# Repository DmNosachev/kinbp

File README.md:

# KinBP
KinBP is a drop-in replacement controller for [Kinesis Contoured keyboards](https://deskthority.net/wiki/Kinesis_Contoured).

It serves the same purpose as [KinT controller](https://github.com/kinx-project/kint) created by Michael Stapelberg.

## Features and advantages
- Controller with [QMK firmware](https://qmk.fm/) support.
- Uses inexpensive [WeAct Studio STM32F401/STM32F411](https://github.com/WeActTC/MiniSTM32F4x1) MCU board. The cost of manufacturing 5 sets is about 12 USD per controller. The PCB has dimensions less than 100×100 mm. Many manufacturers provide additional discounts for smaller boards.
- Compatible with all Kinesis Contoured keyboards but the earliest models (100/110/120).
- Additional pads for connecting up to 8 swithes (i.e. additional switches on the keyboard or foot pedals).
- Replacement thumb cluster PCBs with reversible design. They may be needed for some of 13x models (see below). 
- Thumb cluster switch mounting plates.

## Changelog
1.21
- added 7-pin 1.25mm connector footprints (micro JST) for custom thumb cluster PCBs
- added spare footprints upside down for connectors with pins on the other sideю

## BOM
###  Connectors
The choice of connectors depends on the keyboard model:
 - KB600 (Advantage2).
 1. 6x 13-pin FPC connectors. [Molex 39-53-2135](https://octopart.com/39-53-2135-molex-7670149?r=sp).  Please note that the cheap (5 USD for 20 pcs) [connectors from Aliexpress](https://aliexpress.com/item/1005001616368875.html?item_id=1005001616368875&sku_id=12000016826250362&spm=a2g2w.productlist.0.0.388b79adVkSP7k) are polarised and can only be used for the top row connectors on the KB600; using them in the other positions will not work because the pads on the FPC cable are on the wrong side and the cables are too short to be twisted.

 - KB500 (Advantage).
 1. Connecting keywells and top rows: 4x 13-pin FPC connectors, same as mentioned above.
 2. Connecting thumb cluster PCBs: 2x 10-pin angled 2.54mm headers.

 - KB13x (Essential, Classic, Professional).
 1. Connecting keywell PCBs: 2x [angled 13-pin FPC connectors](https://aliexpress.com/item/32896882494.html?gatewayAdapt=glo2rus&item_id=32896882494&sku_id=65719775344&spm=a2g0s.12269583.0.0.716190456RjJJP).
 2. Connecting top rows: same angled connectors or straight (same as for KB500/KB600).
 3. Some models had LEDs on the thumb cluster PCBs instead of the controller PCB. In this case you will need a pair of new thum cluster PCBs, optional switch mounting plates (see below) and set of cables/connectors with 1.25mm pitch: 2x [7 pin micro JST 10cm cables](https://aliexpress.com/item/4000588750065.html?sku_id=10000003451067244&spm=a2g0o.store_pc_allProduct.8148356.2.6c274451oTiXZp&gatewayAdapt=glo2rus) + 4x [7 pin micro JST angled connector](https://aliexpress.com/item/4000587245338.html?spm=a2g0o.store_pc_allProduct.8148356.8.3bf42024ng7J27&pdp_npi=2%40dis%21RUB%2184%2C24%20%D1%80%D1%83%D0%B1.%2184%2C24%20%D1%80%D1%83%D0%B1.%21%21%21%21%21%40211675ce16784397398875718e4cd2%2110000003439523920%21sh&sku_id=10000003439523925).
 
 Example of incompatible stock thumb cluster PCBc (Kinesis Professional KB134PC): 
 
 You can also reuse connectors from an stock controller, but desoldering them can be tricky. Please note that the Chinese aliexpress connectors and some of the older connectors only had contacts on one side. For the top rows, you need to position the connector so that the contacts are on the outside (there are two footprints for this): 
 
### Controller PCB (/controller-pcb).
  - [WeAct Studio STM32F401 or STM32F411](https://github.com/WeActTC/MiniSTM32F4x1) board. You can buy them for about 6 USD at the [official Aliexpress store](https://weactstudio.aliexpress.com/). Beware of pirated copies!
  
  - 4 pcs 3-mm LEDs
  - 4 pcs 0805 or through-hole resistors. Their value depends on the type of LEDs (I use 1.5k Ohm for orange LEDs).
  - Pair of USB Type C male and female connectors.
###  Thumb cluster (/thumb-pcb)
  - The design is reversible. So, a minimal batch of 5 PCBs will give you 2 pairs + 1 spare.

  - 12x SOD-123 1N4148 diodes.
  - Optional [switch mounting plates](https://github.com/DmNosachev/kin80/tree/main/plates/thumb)
  - set of connectors and cables (see above)
### Switches
  - Optional: 68 pcs Cherry MX compatible switches.
  
## Buid guide
1. Test your keyboard. Identify faulty switches. Decide if you like the switches (most of the time there will Cherry Browns) and the top row rubber buttons. If rubber buttons are unacceptable to you and you do not mind spending a lot of time on hand-wiring, then it is worth considering an alternative project — (Kin80)[https://github.com/DmNosachev/kin80].
2. Disassemble the keyboard. Remove all screws and remove all PCBs. If some of the rubber buttons don't work well, the top row assembly can be taken apart and repaired by sticking pieces of copper tape on the button bottoms. Use hot-melt adhesive to asseble it back.
3. Assemble the controller PCB.
4. Optional: assemble thumb cluster PCBs.
5. Case. Seal the holes on the back of the case with pieces of plastic. Glue the USB connector to the back of the case. Optional: use bitumen sound deadening pads to improve acoustics.
6. [Setup the QMK](https://docs.qmk.fm/).
7. Flash the firmware: `qmk flash -kb kinbp -km default`. Hold 'boot0' button on MCU board, press 'reset', then release 'boot0' to enter bootloader.

## TODO
- FR4 mounting plate for the thumb cluster.
- Create universal or separate PCB with RP2040 support.

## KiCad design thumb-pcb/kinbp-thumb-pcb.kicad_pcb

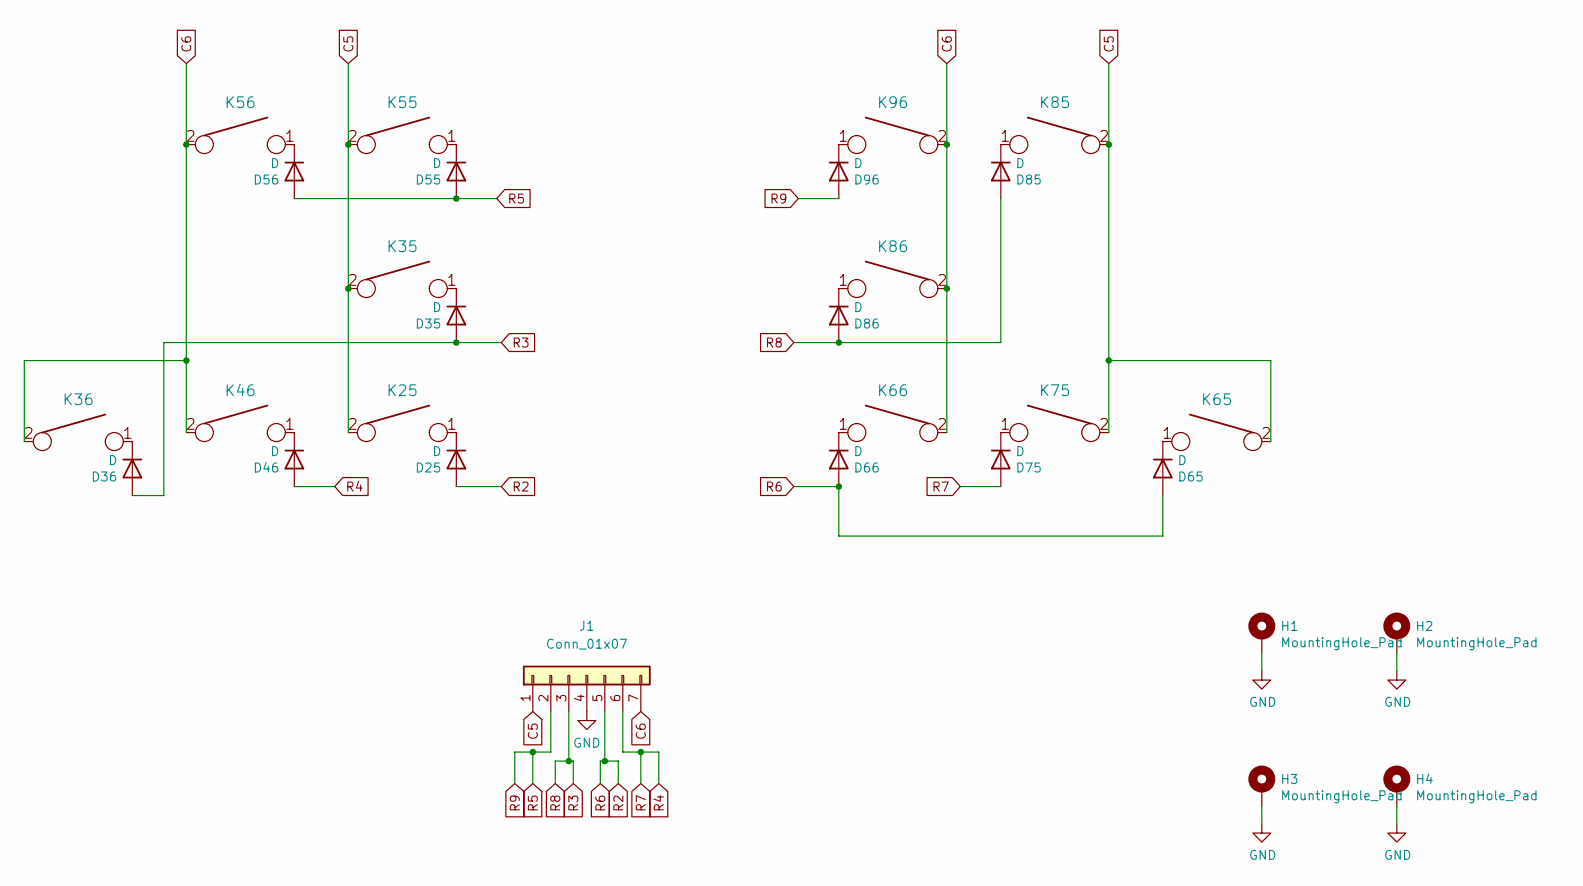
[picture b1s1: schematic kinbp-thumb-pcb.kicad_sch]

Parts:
D25, D35, D36, D46, D55, D56, D65, D66, D75, D85, D86, D96: D; D_SOD-123
H1, H2, H3, H4: MountingHole_Pad; MountingHole_3.7mm_Pad
J1: Conn_01x07; Molex_PicoBlade_53048-0710_1x07_P1.25mm_Horizontal
K25, K35, K36, K46, K55, K56: KEYSW; MXOnly-1U-NoLED-twin
K65, K66, K75, K85, K86, K96: KEYSW; MXOnly-1U-NoLED

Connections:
C5: J1.1, K25.2, K35.2, K55.2, K65.2, K75.2, K85.2
C6: J1.7, K36.2, K46.2, K56.2, K66.2, K86.2, K96.2
GND: H1.1, H2.1, H3.1, H4.1, J1.4
unnamed: D25.1 (K), K25.1
unnamed: D35.1 (K), K35.1
unnamed: D36.1 (K), K36.1
unnamed: D46.1 (K), K46.1
unnamed: D55.1 (K), K55.1
unnamed: D56.1 (K), K56.1
unnamed: D65.1 (K), K65.1
unnamed: D66.1 (K), K66.1
unnamed: D75.1 (K), K75.1
unnamed: D85.1 (K), K85.1
unnamed: D86.1 (K), K86.1
unnamed: D96.1 (K), K96.1
R2: D25.2 (A), D65.2 (A), D66.2 (A), J1.5
R3: D35.2 (A), D36.2 (A), D85.2 (A), D86.2 (A), J1.3
R4: D46.2 (A), D75.2 (A), J1.6
R5: D55.2 (A), D56.2 (A), D96.2 (A), J1.2

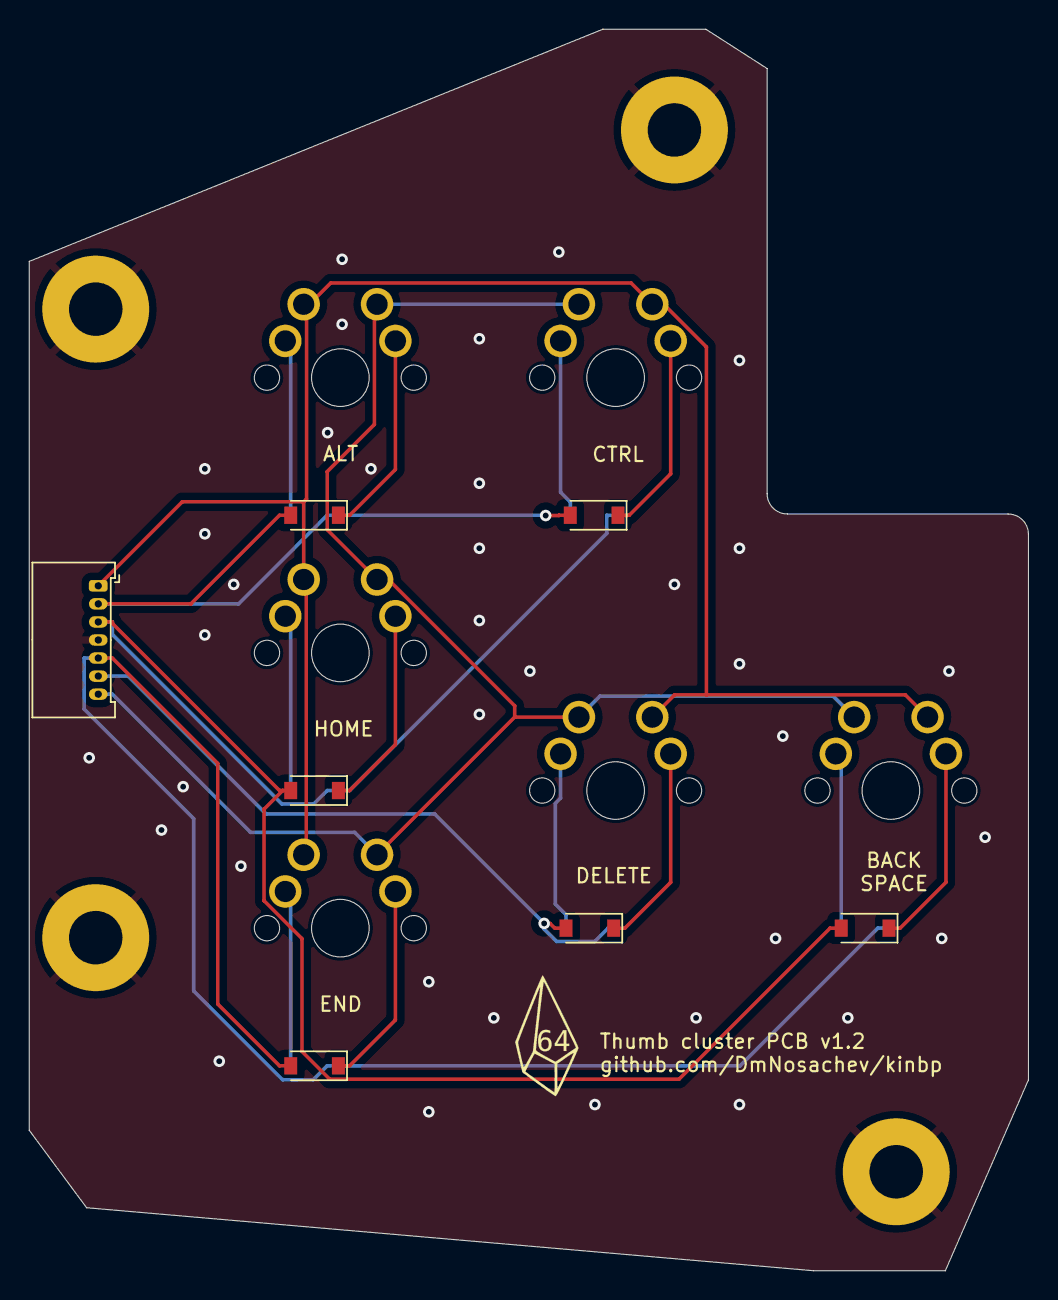
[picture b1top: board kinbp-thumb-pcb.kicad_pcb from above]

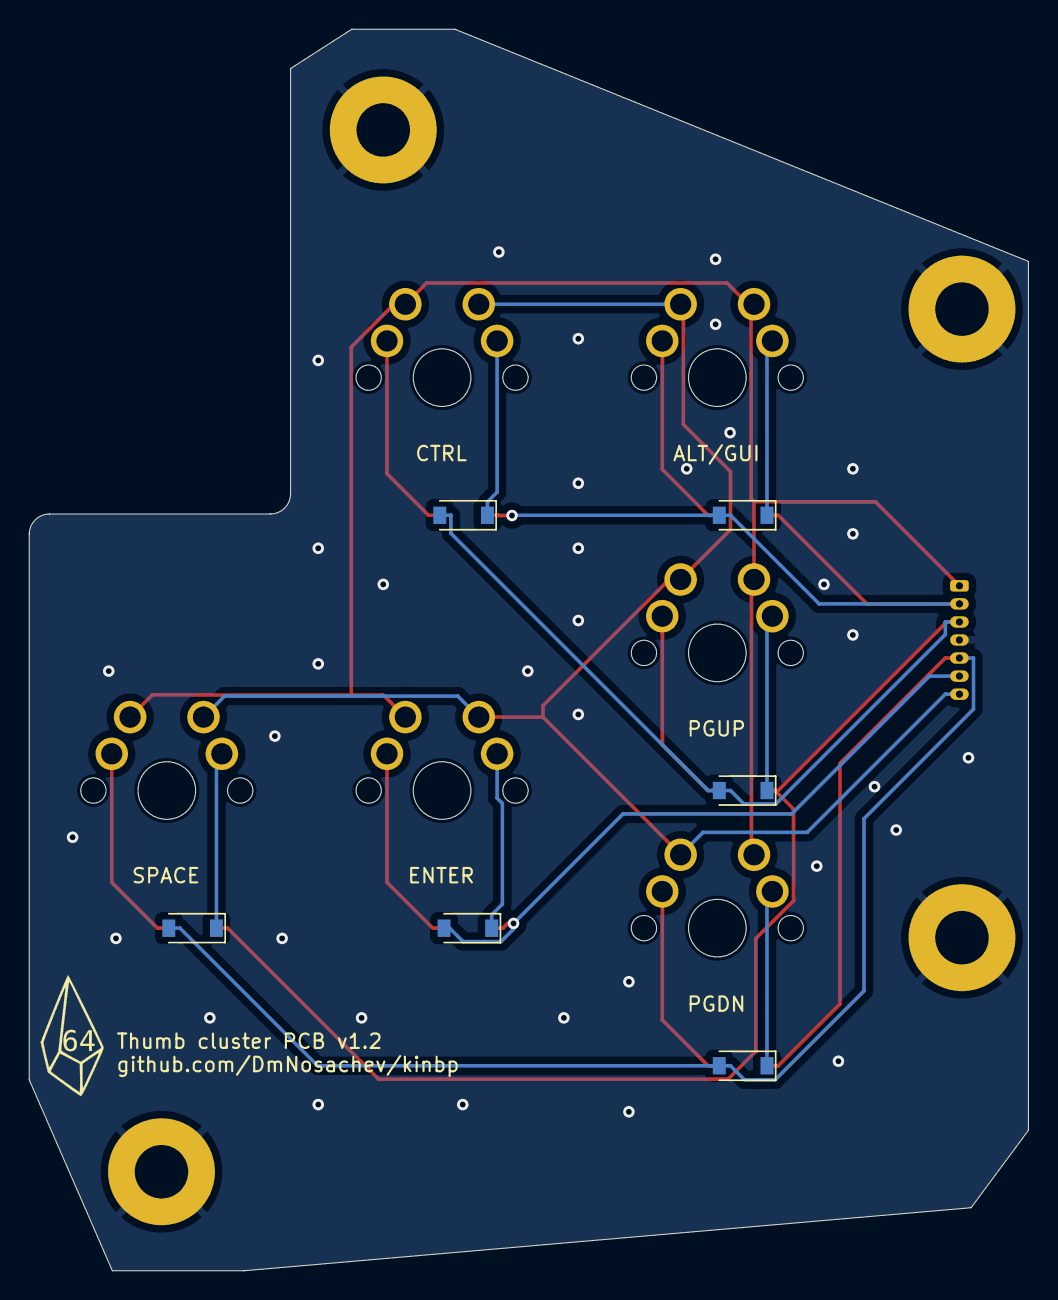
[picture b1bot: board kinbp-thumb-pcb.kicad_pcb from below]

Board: 2 copper layers, 69.2 x 85.9 mm, 31 parts (13 on the bottom side), 19 nets.

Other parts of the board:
G1, G2: LOGO; q64logo

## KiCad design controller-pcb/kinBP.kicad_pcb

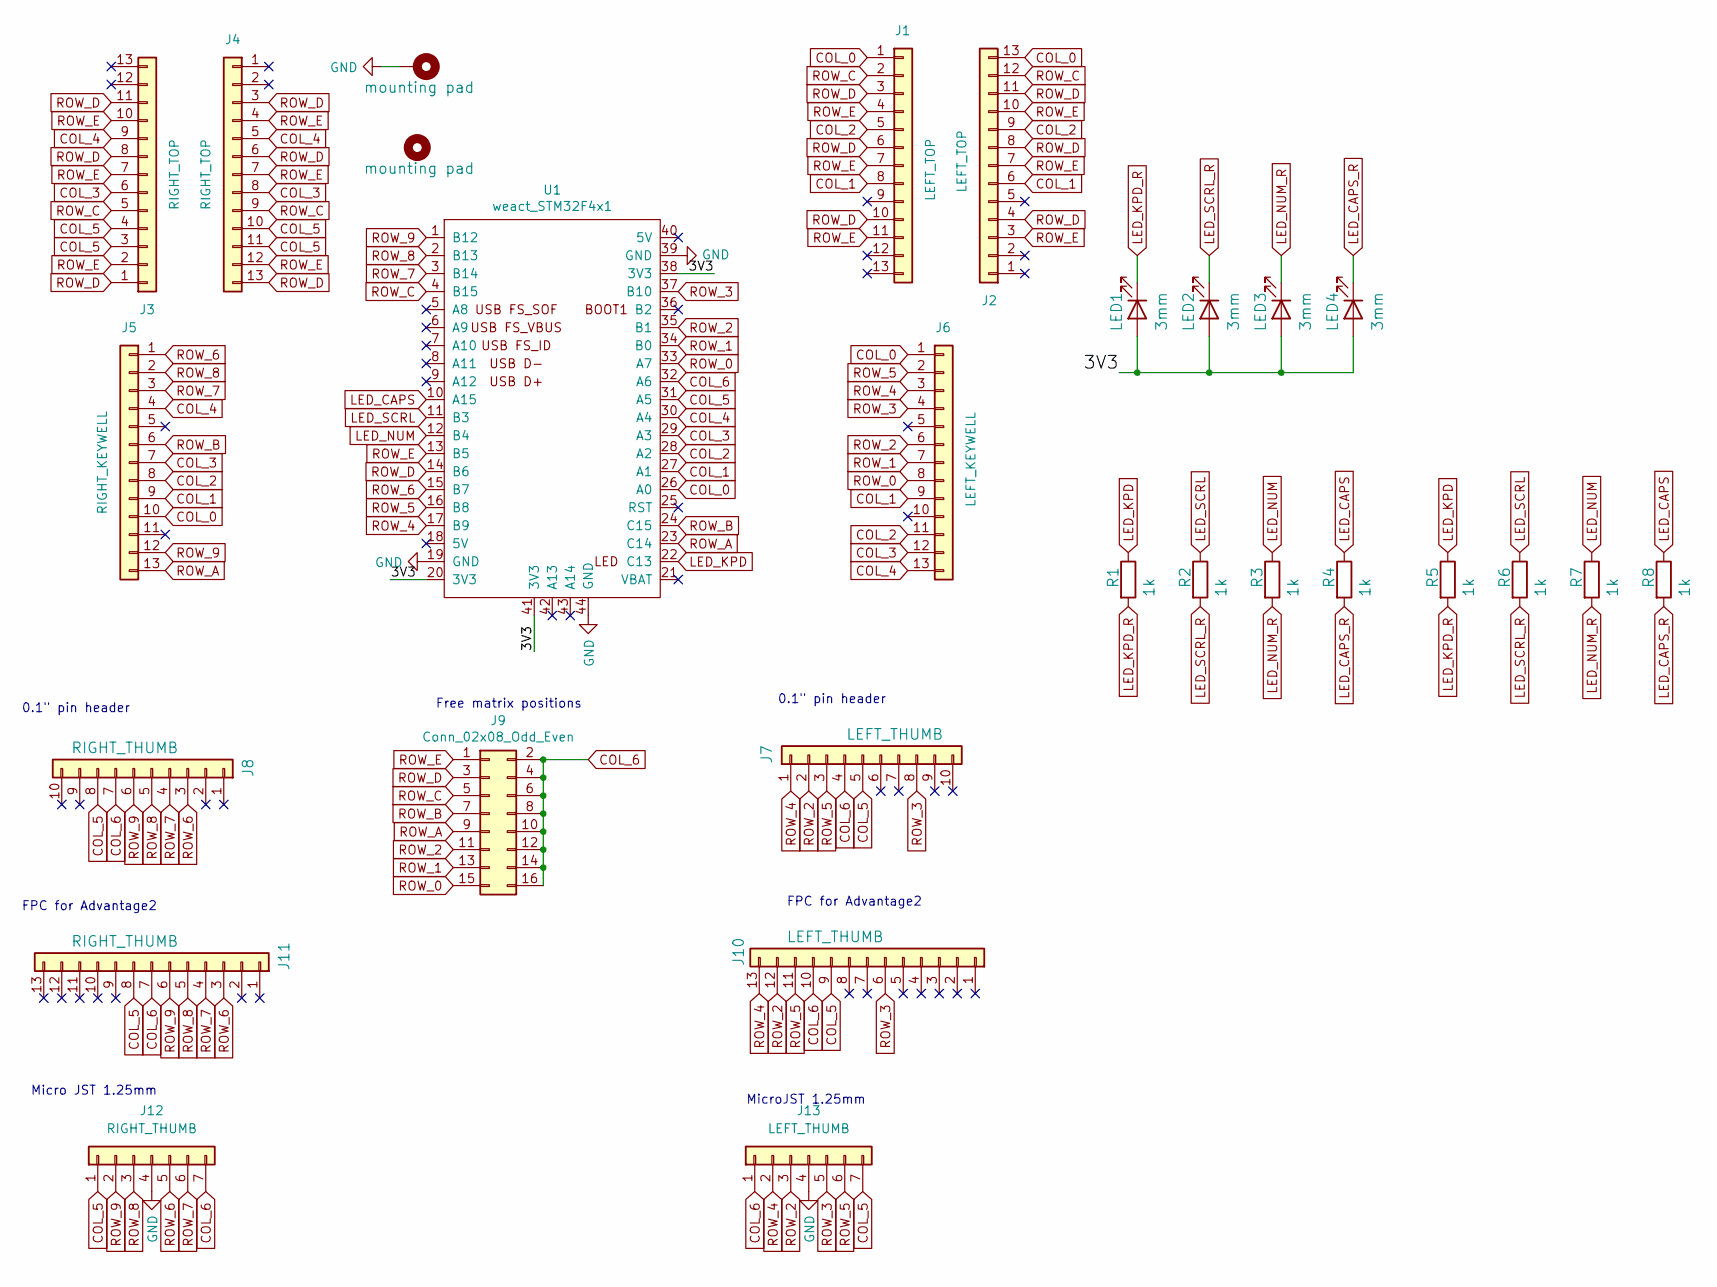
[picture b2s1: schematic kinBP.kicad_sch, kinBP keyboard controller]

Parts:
H1: mounting pad; MountingHole_4.3mm_M4_Pad
H2: mounting pad; MountingHole_6mm
J1, J2: LEFT_TOP; 39-53-2135
J3, J4: RIGHT_TOP; 39-53-2135
J5: RIGHT_KEYWELL; 39-53-2135
J6: LEFT_KEYWELL; 39-53-2135
J7: LEFT_THUMB; PinHeader_1x10_P2.54mm_Vertical
J8: RIGHT_THUMB; PinHeader_1x10_P2.54mm_Vertical
J9: Conn_02x08_Odd_Even; PinHeader_2x08_P2.54mm_Vertical
J10: LEFT_THUMB; 39-53-2135
J11: RIGHT_THUMB; 39-53-2135
J12: RIGHT_THUMB; Molex_PicoBlade_53048-0710_1x07_P1.25mm_Horizontal
J13: LEFT_THUMB; Molex_PicoBlade_53048-0710_1x07_P1.25mm_Horizontal
LED1, LED2, LED3, LED4: 3mm; LED_D3.0mm
R1, R2, R3, R4: 1k; R_0805_2012Metric_Pad1.20x1.40mm_HandSolder
R5, R6, R7, R8: 1k; R_Axial_DIN0207_L6.3mm_D2.5mm_P7.62mm_Horizontal
U1: weact_STM32F4x1; STM32F4x1_MiniF4

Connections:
/3V3: LED1.2 (A), LED2.2 (A), LED3.2 (A), LED4.2 (A), U1.20 (3V3), U1.38 (3V3), U1.41 (3V3)
COL_0: J1.1, J2.13, J5.10, J6.1, U1.26 (A0)
COL_1: J1.8, J2.6, J5.9, J6.9, U1.27 (A1)
COL_2: J1.5, J2.9, J5.8, J6.11, U1.28 (A2)
COL_3: J3.6, J4.8, J5.7, J6.12, U1.29 (A3)
COL_4: J3.9, J4.5, J5.4, J6.13, U1.30 (A4)
COL_5: J3.3, J3.4, J4.10, J4.11, J7.5, J8.8, J10.9, J11.8, J12.1, J13.7, U1.31 (A5)
COL_6: J7.4, J8.7, J9.2, J9.4, J9.6, J9.8, J9.10, J9.12, J9.14, J9.16, J10.10, J11.7, J12.7, J13.1, U1.32 (A6)
GND: H1.1, J12.4, J13.4, U1.19 (GND), U1.39 (GND), U1.44 (GND)
LED_CAPS: R4.1, R8.1, U1.10 (A15)
LED_CAPS_R: LED4.1 (K), R4.2, R8.2
LED_KPD: R1.1, R5.1, U1.22 (C13)
LED_KPD_R: LED1.1 (K), R1.2, R5.2
LED_NUM: R3.1, R7.1, U1.12 (B4)
LED_NUM_R: LED3.1 (K), R3.2, R7.2
LED_SCRL: R2.1, R6.1, U1.11 (B3)
LED_SCRL_R: LED2.1 (K), R2.2, R6.2
ROW_0: J6.8, J9.15, U1.33 (A7)
ROW_1: J6.7, J9.13, U1.34 (B0)
ROW_2: J6.6, J7.2, J9.11, J10.12, J13.3, U1.35 (B1)
ROW_3: J6.4, J7.8, J10.6, J13.5, U1.37 (B10)
ROW_4: J6.3, J7.1, J10.13, J13.2, U1.17 (B9)
ROW_5: J6.2, J7.3, J10.11, J13.6, U1.16 (B8)
ROW_6: J5.1, J8.3, J11.3, J12.5, U1.15 (B7)
ROW_7: J5.3, J8.4, J11.4, J12.6, U1.3 (B14)
ROW_8: J5.2, J8.5, J11.5, J12.3, U1.2 (B13)
ROW_9: J5.12, J8.6, J11.6, J12.2, U1.1 (B12)
ROW_A: J5.13, J9.9, U1.23 (C14)
ROW_B: J5.6, J9.7, U1.24 (C15)
ROW_C: J1.2, J2.12, J3.5, J4.9, J9.5, U1.4 (B15)
ROW_D: J1.3, J1.6, J1.10, J2.4, J2.8, J2.11, J3.1, J3.8, J3.11, J4.3, J4.6, J4.13, J9.3, U1.14 (B6)
ROW_E: J1.4, J1.7, J1.11, J2.3, J2.7, J2.10, J3.2, J3.7, J3.10, J4.4, J4.7, J4.12, J9.1, U1.13 (B5)

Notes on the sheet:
FPC for Advantage2
0.1" pin header
MicroJST 1.25mm
Micro JST 1.25mm
Free matrix positions

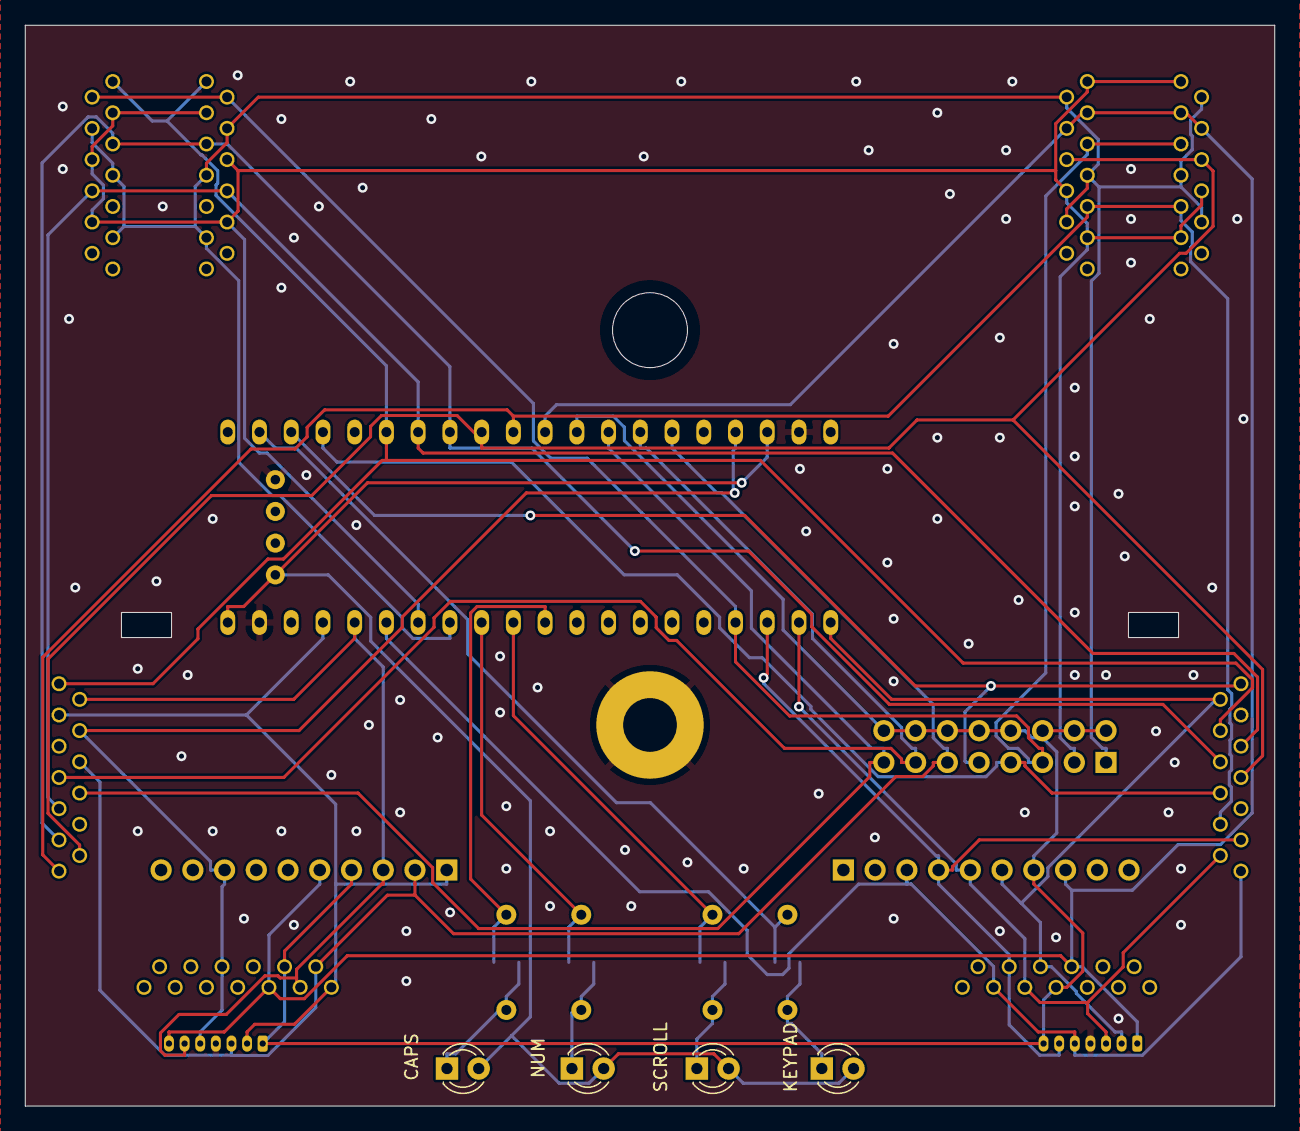
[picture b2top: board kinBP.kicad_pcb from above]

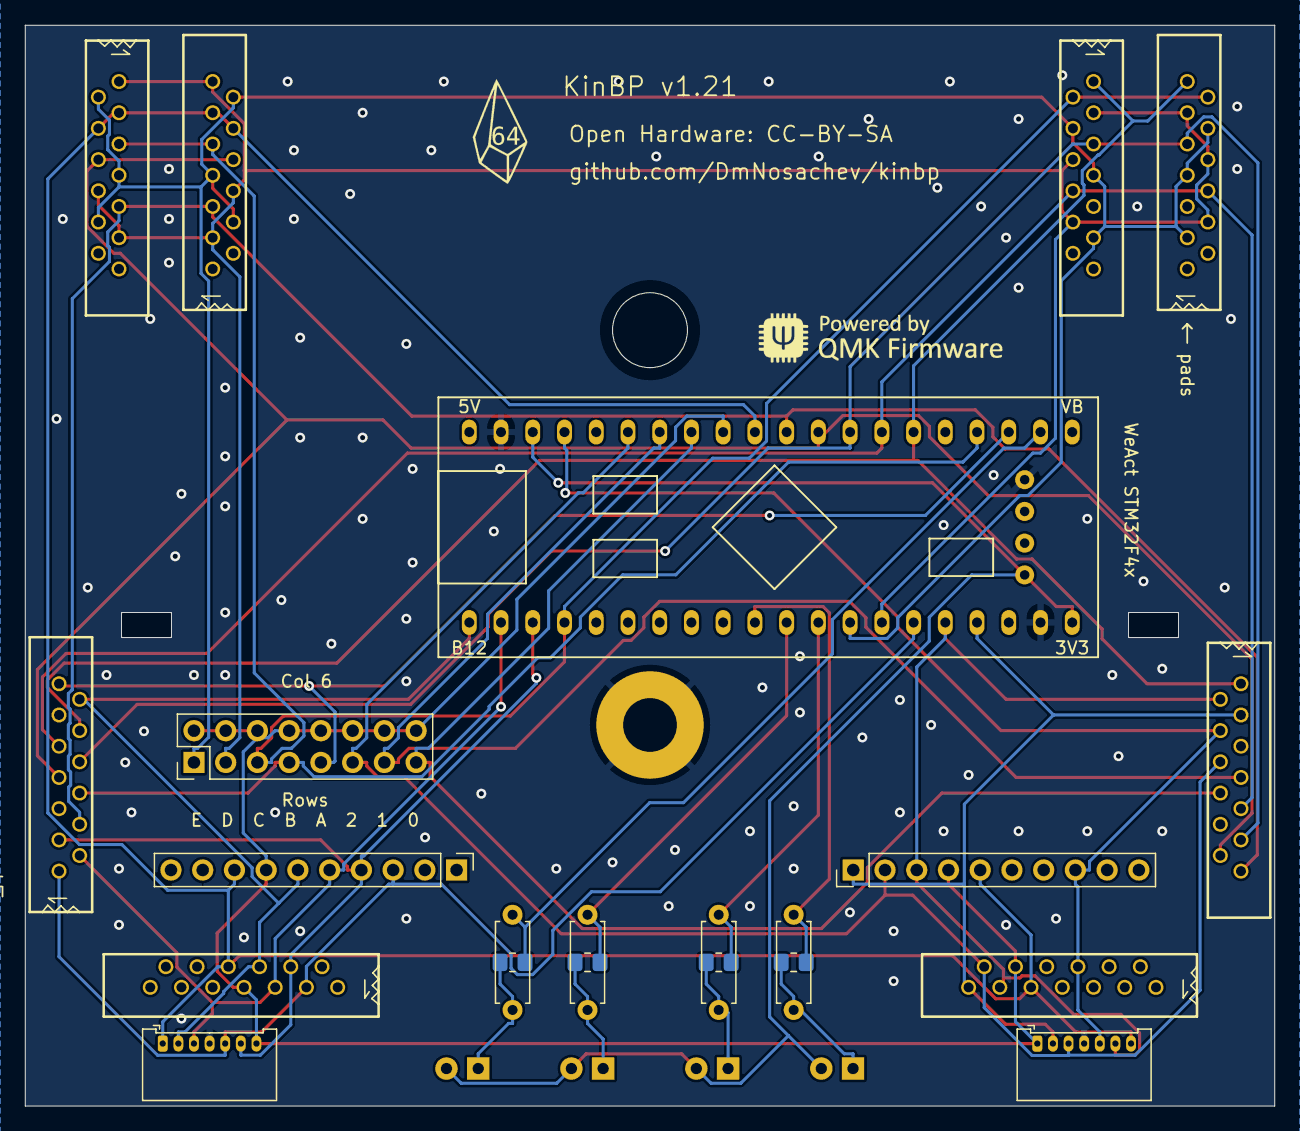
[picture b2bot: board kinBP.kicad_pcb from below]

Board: 2 copper layers, 100.0 x 86.5 mm, 29 parts (23 on the bottom side), 32 nets.

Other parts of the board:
G1: LOGO; q64logo

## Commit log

2023-12-13 README.md: Clarify incompatibility of cheap Aliexpress FPC connectors
    This one sentence in the README.md cost me a bunch of time, money,
    wasted components and possibly a whole PCB. One is not amused.

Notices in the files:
controller-pcb/kinBP.kicad_pcb:
Open Hardware: CC-BY-SA
